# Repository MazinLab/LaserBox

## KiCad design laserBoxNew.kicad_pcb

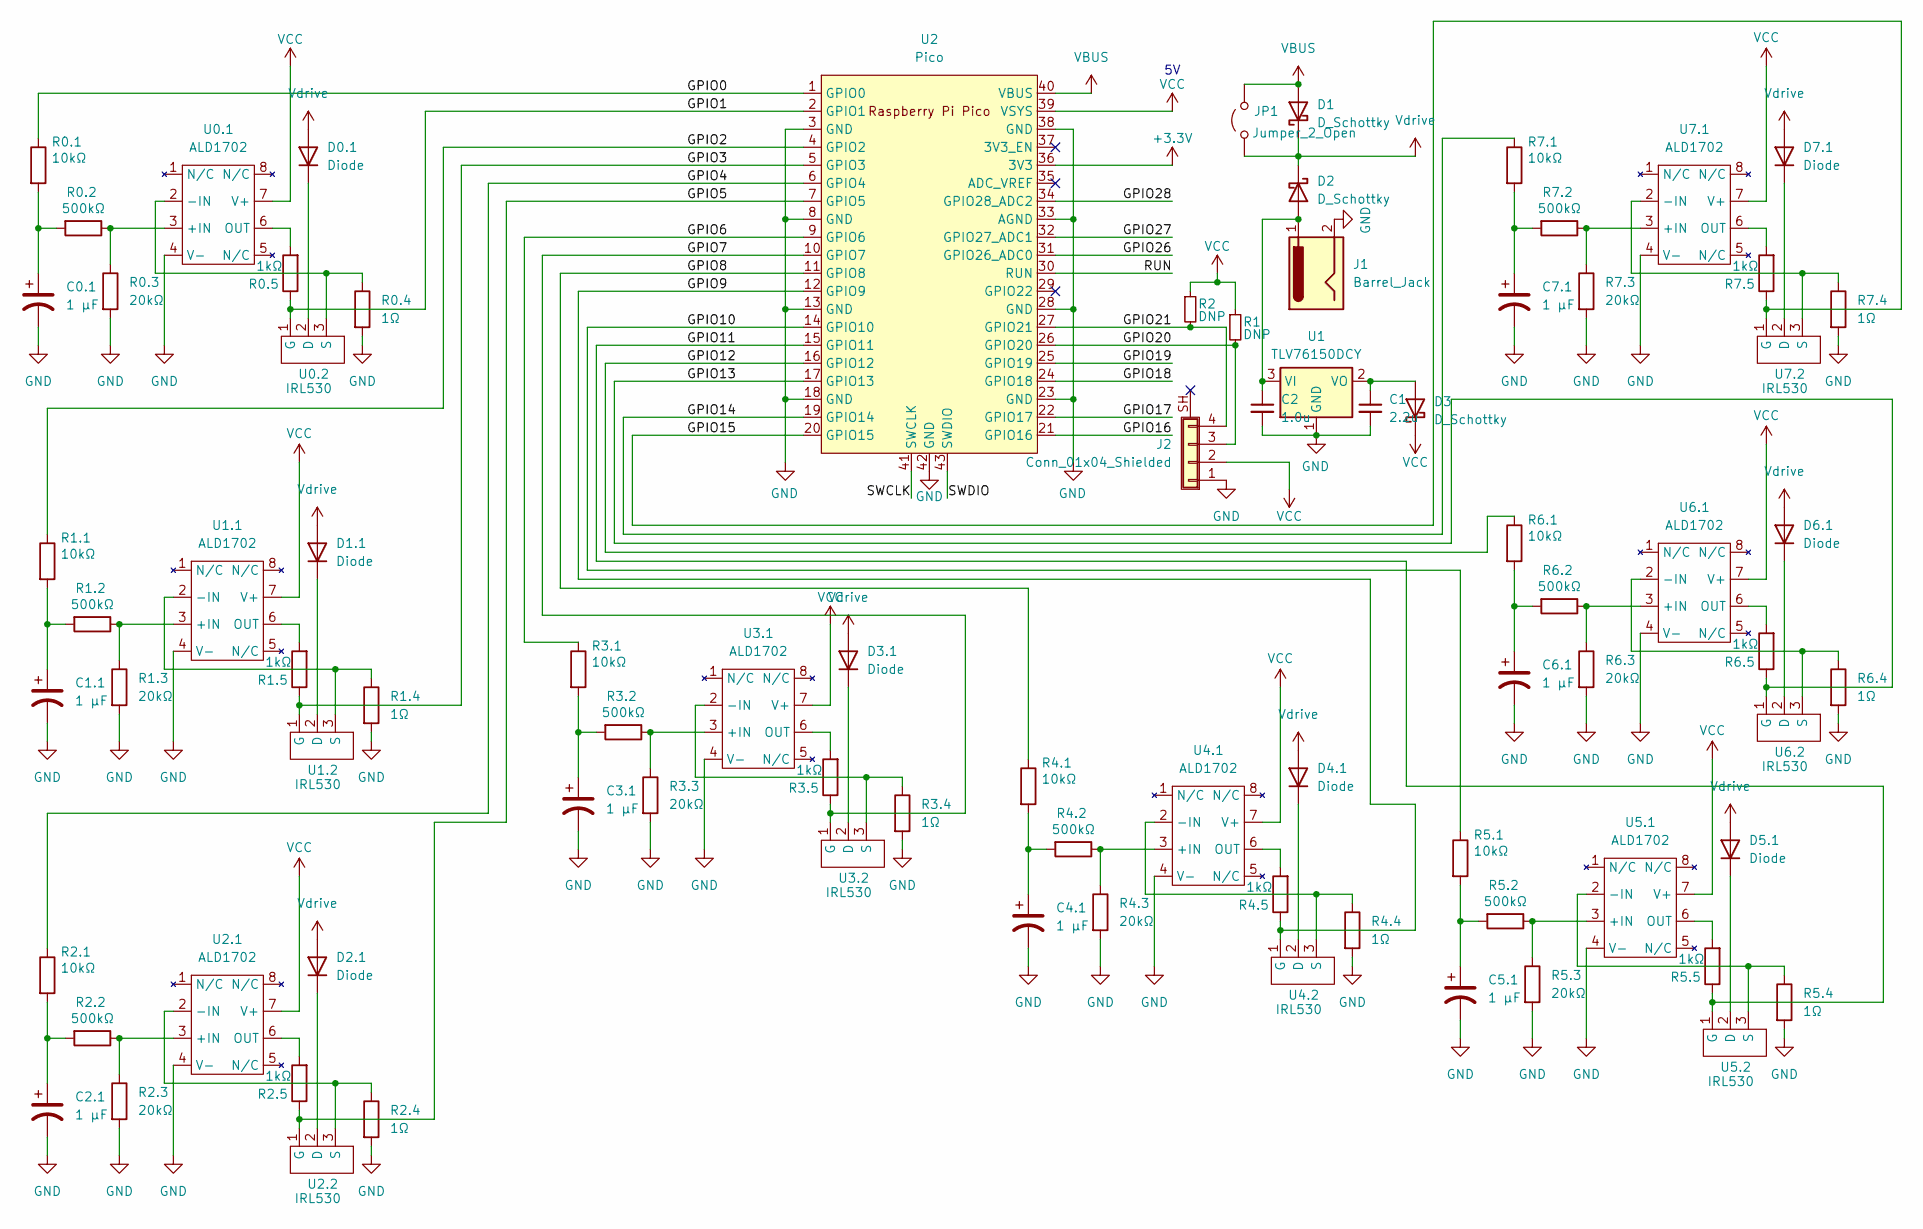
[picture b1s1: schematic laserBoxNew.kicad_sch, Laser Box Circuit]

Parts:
C0.1, C1.1, C2.1, C3.1, C4.1, C5.1, C6.1, C7.1: 1 μF; C_0603_1608Metric
C1: 2.2u; C_0603_1608Metric
C2: 1.0u; C_0603_1608Metric
D0.1, D1.1, D2.1, D3.1, D4.1, D5.1, D6.1, D7.1: Diode; Molex_PicoBlade_53398-0271_1x02-1MP_P1.25mm_Vertical
D1, D2, D3: D_Schottky; MBR120_SOD-123
J1: Barrel_Jack; BarrelJack_CUI_PJ-063AH_Horizontal
J2: Conn_01x04_Shielded; JST_SH_SM04B-SRSS-TB_1x04-1MP_P1.00mm_Horizontal
JP1: Jumper_2_Open; SolderJumper-2_P1.3mm_Open_Pad1.0x1.5mm
R0.1, R1.1, R2.1, R3.1, R4.1, R5.1, R6.1, R7.1: 10kΩ; R_0603_1608Metric
R0.2, R1.2, R2.2, R3.2, R4.2, R5.2, R6.2, R7.2: 500kΩ; R_0603_1608Metric
R0.3, R1.3, R2.3, R3.3, R4.3, R5.3, R6.3, R7.3: 20kΩ; R_0603_1608Metric
R0.4, R1.4, R2.4, R3.4, R4.4, R5.4, R6.4, R7.4: 1Ω; R_0603_1608Metric
R0.5, R1.5, R2.5, R3.5, R4.5, R5.5, R6.5, R7.5: 1kΩ; R_0603_1608Metric
R1, R2: DNP; R_0603_1608Metric
U0.1, U1.1, U2.1, U3.1, U4.1, U5.1, U6.1, U7.1: ALD1702; SOIC-8-1EP_3.9x4.9mm_P1.27mm_EP2.514x3.2mm
U0.2, U1.2, U2.2, U3.2, U4.2, U5.2, U6.2, U7.2: IRL530; TO-220-3_Vertical
U1: TLV76150DCY; SOT-223-3_TabPin2
U2: Pico; RPi_Pico_SMD_TH

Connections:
+3.3V: U2.36 (3V3)
/GPIO0: R0.1.1, U2.1 (GPIO0)
/GPIO1: R0.5.1, U0.2.1 (G), U2.2 (GPIO1)
/GPIO2: R1.1.1, U2.4 (GPIO2)
/GPIO3: R1.5.1, U1.2.1 (G), U2.5 (GPIO3)
/GPIO4: R2.1.1, U2.6 (GPIO4)
/GPIO5: R2.5.1, U2.7 (GPIO5), U2.2.1 (G)
/GPIO6: R3.1.1, U2.9 (GPIO6)
/GPIO7: R3.5.1, U2.10 (GPIO7), U3.2.1 (G)
/GPIO8: R4.1.1, U2.11 (GPIO8)
/GPIO9: R4.5.1, U2.12 (GPIO9), U4.2.1 (G)
/GPIO10: R5.1.1, U2.14 (GPIO10)
/GPIO11: R5.5.1, U2.15 (GPIO11), U5.2.1 (G)
/GPIO12: R6.1.1, U2.16 (GPIO12)
/GPIO13: R6.5.1, U2.17 (GPIO13), U6.2.1 (G)
/GPIO14: R7.1.1, U2.19 (GPIO14)
/GPIO15: R7.5.1, U2.20 (GPIO15), U7.2.1 (G)
/GPIO16: U2.21 (GPIO16)
/GPIO17: U2.22 (GPIO17)
/GPIO18: U2.24 (GPIO18)
/GPIO19: U2.25 (GPIO19)
/GPIO20: J2.3, R1.2, U2.26 (GPIO20)
/GPIO21: J2.4, R2.2, U2.27 (GPIO21)
/GPIO26: U2.31 (GPIO26_ADC0)
/GPIO27: U2.32 (GPIO27_ADC1)
/GPIO28: U2.34 (GPIO28_ADC2)
/RUN: U2.30 (RUN)
/SWCLK: U2.41 (SWCLK)
/SWDIO: U2.43 (SWDIO)
GND: C0.1.2, C1.2, C1.1.2, C2.2, C2.1.2, C3.1.2, C4.1.2, C5.1.2, C6.1.2, C7.1.2, J1.2, J2.1, R0.3.2, R0.4.2, R1.3.2, R1.4.2, R2.3.2, R2.4.2, R3.3.2, R3.4.2, R4.3.2, R4.4.2, R5.3.2, R5.4.2, R6.3.2, R6.4.2, R7.3.2, R7.4.2, U0.1.4 (V-), U1.1 (GND), U1.1.4 (V-), U2.3 (GND), U2.8 (GND), U2.13 (GND), U2.18 (GND), U2.23 (GND), U2.28 (GND), U2.33 (AGND), U2.38 (GND), U2.42 (GND), U2.1.4 (V-), U3.1.4 (V-), U4.1.4 (V-), U5.1.4 (V-), U6.1.4 (V-), U7.1.4 (V-)
unnamed: C0.1.1, R0.1.2, R0.2.2
unnamed: C1.1.1, R1.1.2, R1.2.2
unnamed: C2.1.1, R2.1.2, R2.2.2
unnamed: C3.1.1, R3.1.2, R3.2.2
unnamed: C4.1.1, R4.1.2, R4.2.2
unnamed: C5.1.1, R5.1.2, R5.2.2
unnamed: C6.1.1, R6.1.2, R6.2.2
unnamed: C7.1.1, R7.1.2, R7.2.2
unnamed: D0.1.1 (K), U0.2.2 (D)
unnamed: D1.1.1 (K), U1.2.2 (D)
unnamed: C2.1, D2.2 (A), J1.1, U1.3 (VI)
unnamed: D2.1.1 (K), U2.2.2 (D)
unnamed: C1.1, D3.2 (A), U1.2 (VO)
unnamed: D3.1.1 (K), U3.2.2 (D)
unnamed: D4.1.1 (K), U4.2.2 (D)
unnamed: D5.1.1 (K), U5.2.2 (D)
unnamed: D6.1.1 (K), U6.2.2 (D)
unnamed: D7.1.1 (K), U7.2.2 (D)
unnamed: R0.2.1, R0.3.1, U0.1.3 (+IN)
unnamed: R0.4.1, U0.1.2 (-IN), U0.2.3 (S)
unnamed: R0.5.2, U0.1.6 (OUT)
unnamed: R1.2.1, R1.3.1, U1.1.3 (+IN)
unnamed: R1.4.1, U1.1.2 (-IN), U1.2.3 (S)
unnamed: R1.5.2, U1.1.6 (OUT)
unnamed: R2.2.1, R2.3.1, U2.1.3 (+IN)
unnamed: R2.4.1, U2.1.2 (-IN), U2.2.3 (S)
unnamed: R2.5.2, U2.1.6 (OUT)
unnamed: R3.2.1, R3.3.1, U3.1.3 (+IN)
unnamed: R3.4.1, U3.1.2 (-IN), U3.2.3 (S)
unnamed: R3.5.2, U3.1.6 (OUT)
unnamed: R4.2.1, R4.3.1, U4.1.3 (+IN)
unnamed: R4.4.1, U4.1.2 (-IN), U4.2.3 (S)
unnamed: R4.5.2, U4.1.6 (OUT)
unnamed: R5.2.1, R5.3.1, U5.1.3 (+IN)
unnamed: R5.4.1, U5.1.2 (-IN), U5.2.3 (S)
unnamed: R5.5.2, U5.1.6 (OUT)
unnamed: R6.2.1, R6.3.1, U6.1.3 (+IN)
unnamed: R6.4.1, U6.1.2 (-IN), U6.2.3 (S)
unnamed: R6.5.2, U6.1.6 (OUT)
unnamed: R7.2.1, R7.3.1, U7.1.3 (+IN)
unnamed: R7.4.1, U7.1.2 (-IN), U7.2.3 (S)
unnamed: R7.5.2, U7.1.6 (OUT)
VBUS: D1.2 (A), JP1.2 (B), U2.40 (VBUS)
VCC: D3.1 (K), J2.2, R1.1, R2.1, U0.1.7 (V+), U1.1.7 (V+), U2.39 (VSYS), U2.1.7 (V+), U3.1.7 (V+), U4.1.7 (V+), U5.1.7 (V+), U6.1.7 (V+), U7.1.7 (V+)
Vdrive: D0.1.2 (A), D1.1 (K), D1.1.2 (A), D2.1 (K), D2.1.2 (A), D3.1.2 (A), D4.1.2 (A), D5.1.2 (A), D6.1.2 (A), D7.1.2 (A), JP1.1 (A)

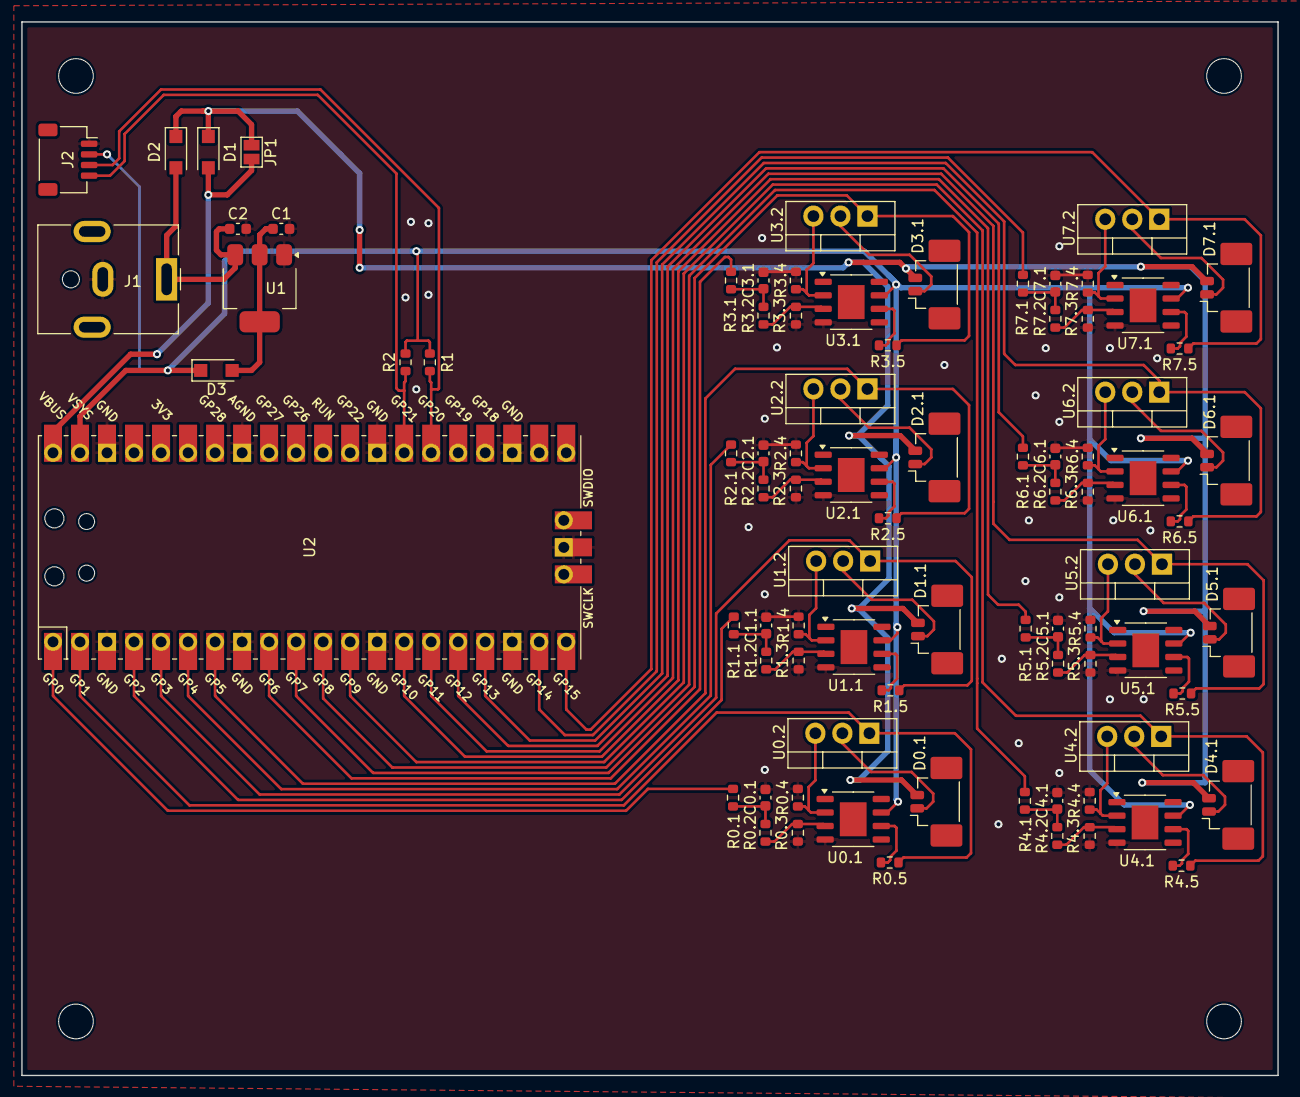
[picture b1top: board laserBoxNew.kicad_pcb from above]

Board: 2 copper layers, 118.1 x 99.1 mm, 84 parts (0 on the bottom side), 64 nets.

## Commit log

2024-09-04 Add unziped version
